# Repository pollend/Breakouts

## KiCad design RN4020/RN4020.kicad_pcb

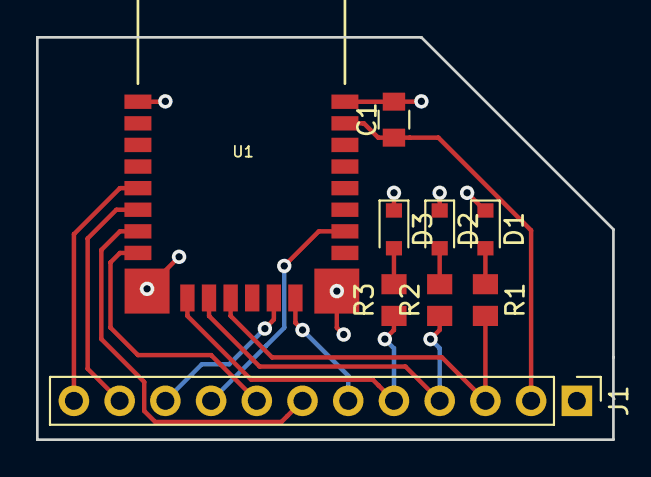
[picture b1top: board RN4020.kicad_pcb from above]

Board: 2 copper layers, 32.0 x 22.4 mm, 9 parts (0 on the bottom side), 15 nets.

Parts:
C1: 4.7uF; C_0805
D1: Blue; D_0805
D2: Red; D_0805
D3: Green; D_0805
J1: Conn_01x12; PinHeader_1x12_P2.54mm_Vertical
R1, R2, R3: 330; R_0805_2012Metric
U1: RN4020

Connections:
+3V3: C1.1, J1.2, U1.23
BT_UART_CTS: J1.10, U1.14
BT_UART_RTS: J1.9, U1.18
BT_WAKE: J1.6, U1.15
CMD_MLDP: J1.8, U1.8
CONNECTION_STATUS: J1.5, R3.1, U1.10
GND: C1.2, D1.1, D2.1, D3.1, J1.1, U1.1, U1.9, U1.16, U1.24
MLDP_EV: J1.4, R2.1, U1.11
unnamed: D1.2, R1.1
unnamed: D2.2, R2.2
unnamed: D3.2, R3.2
RX: J1.11, U1.6
SWAKE: J1.7, U1.7
TX: J1.12, U1.5
WS: J1.3, R1.2, U1.12

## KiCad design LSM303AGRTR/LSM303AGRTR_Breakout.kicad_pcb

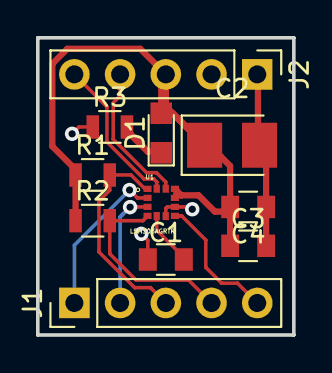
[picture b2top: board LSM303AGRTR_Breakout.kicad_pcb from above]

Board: 2 copper layers, 14.2 x 16.5 mm, 11 parts (0 on the bottom side), 11 nets.

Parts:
C1: 220nF; C_0805
C2: 10uF; CP_Tantalum_Case-T_EIA-3528-12_Reflow
C3, C4: 100nF; C_0805
D1: LED; LED_0805
J1, J2: Conn_01x05; Pin_Header_Straight_1x05_Pitch2.54mm
R1, R2, R3: 10K; R_0805
U1: LSM303AGRTR; LGA12R50P_200X200X100

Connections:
+3V3: C2.1, C3.1, C4.2, D1.2, J2.3, R1.1, R2.1, U1.9, U1.10
CS_MAG: J1.2, U1.3
CS_XL: J1.1, U1.2
GND: C1.1, C2.2, C3.2, C4.1, J2.1, J2.2, R3.1, U1.6, U1.8
INT_1_XL: J2.5, U1.12
INT_2_XL: J2.4, U1.11
INT_MAG: J1.5, U1.7
unnamed: C1.2, U1.5
unnamed: D1.1, R3.2
SCL: J1.3, R1.2, U1.1
SDA: J1.4, R2.2, U1.4

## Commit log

2018-05-04 added breakouts
2018-05-04 added RN4020 breakout
